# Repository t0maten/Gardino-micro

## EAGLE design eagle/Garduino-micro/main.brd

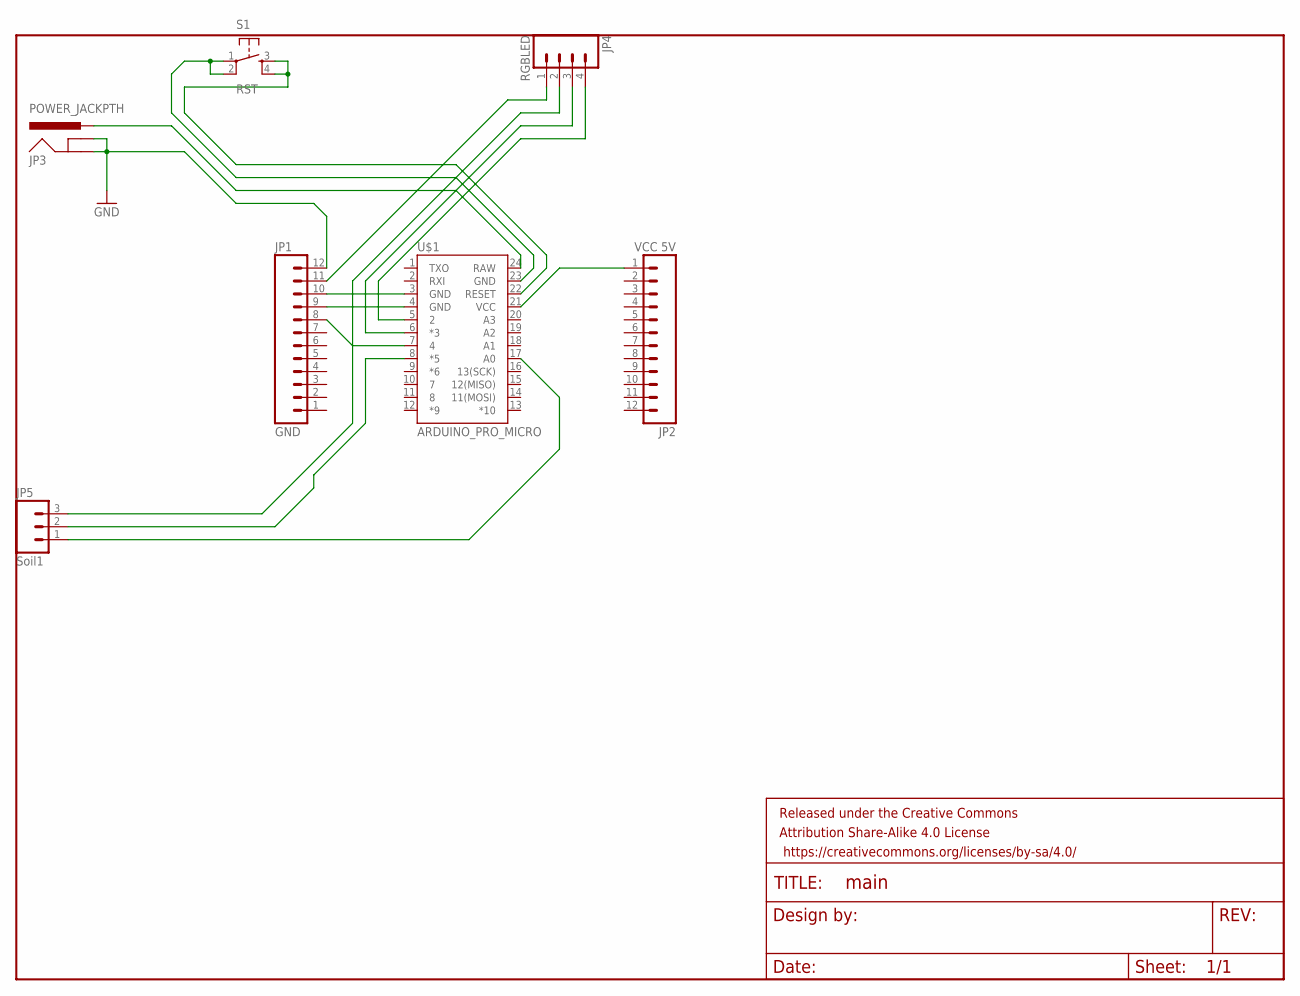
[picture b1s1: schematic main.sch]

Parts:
JP1: GND; 1X12_LONGPADS
JP2: VCC 5V; 1X12_LONGPADS
JP3: POWER_JACKPTH; POWER_JACK_PTH
JP4: RGBLED; JST-4-PTH-VERT
JP5: Soil1; JST-3-PTH
MAIN_PCB_FRAME: Main frame PCB; DUMMY
S1: RST; TACTILE-PTH
U$1: ARDUINO_PRO_MICRO

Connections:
GND: JP1.12, JP3.GND, JP3.GNDBREAK
unnamed: JP2.1, U$1.21 (VCC)
unnamed: JP4.4, U$1.5 (2)
unnamed: S1.1, S1.2, U$1.23 (GND)
unnamed: JP3.PWR, U$1.24 (RAW)
unnamed: JP1.10, U$1.3 (GND)
unnamed: S1.3, S1.4, U$1.22 (RESET)
unnamed: JP1.9, U$1.4 (GND)
unnamed: JP4.3, U$1.6 (*3)
unnamed: JP4.2, U$1.7 (4)
unnamed: JP1.11, JP4.1
unnamed: JP1.8, JP5.3
unnamed: JP5.2, U$1.8 (*5)
unnamed: JP5.1, U$1.17 (A0)

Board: 2 copper layers, 8 parts (0 on the bottom side), 14 nets, no tracks yet.

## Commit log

2015-04-26 :neckbeard: Added .gitattributes
2015-04-26 Main file
2015-04-26 Soil levels and led warnings
2015-04-27 more stuff
2015-04-28 added libs and stuff
2015-04-28 played around with libs

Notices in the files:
parts and their libraries:
SparkFun-Connectors: Licensing: Creative Commons ShareAlike 4.0 International - https://creativecommons.org/licenses/by-sa/4.0
SparkFun-Aesthetics: Released under the Creative Commons Attribution Share-Alike 4.0 License
SparkFun-Aesthetics: https://creativecommons.org/licenses/by-sa/4.0
